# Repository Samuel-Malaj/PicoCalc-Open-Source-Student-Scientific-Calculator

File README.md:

# PicoCalc-Open-Source-Student-Scientific-Calculator
Open source scientific calculator built on Raspberry Pi Pico W — custom PCB, WiFi messaging, IR projector control and games.

# PicoCalc — Open Source Student Scientific Calculator

A fully custom scientific calculator built on the Raspberry Pi Pico W, designed specifically for students. Features wireless peer-to-peer messaging, IR classroom projector control, a custom PCB, and built-in games — all running on MicroPython.

---

## Overview

PicoCalc is an end-to-end hardware and software project encompassing PCB design, embedded systems programming, wireless networking, and circuit design. Every component — from the button matrix to the IR driver circuit — was designed, calculated, and implemented from scratch.

This project was built entirely by a Year 10/11 student as an independent engineering project.

---

## Features

### Scientific Calculator
- Full arithmetic operations with correct operator precedence
- Scientific functions: sin, cos, tan, log, ln, sqrt, powers, factorials
- Degree and radian mode switching
- Expression history and ANS recall
- Error handling for invalid inputs and edge cases
- Custom expression parser built from scratch in MicroPython

### Peer-to-Peer Messaging
- Send and receive text messages between two PicoCalc devices over WiFi
- UDP broadcast protocol for low-latency local communication
- Designed for classroom use — share working, answers, or notes with a friend

### IR Projector Control
- 940nm IR LED with BC547 transistor driver circuit
- Compatible with Hitachi, Maxell, Epson and Samsung projectors and displays
- Up to 10 metre range achieved through transistor amplification
- Allows students to control classroom projectors from their desk
- NEC and SIRC IR protocol support

### Games
- Built-in simple games for use during breaks
- Runs entirely on the calculator hardware — no additional software needed

---

## Hardware

### Custom PCB
- Designed from scratch in KiCad
- Manufactured by PCBWay
- 2-layer PCB with row traces on F.Cu and column traces on B.Cu
- Dimensions: 75.5mm × 146mm

### Components
| Component | Description |
|---|---|
| Raspberry Pi Pico W | Main microcontroller with WiFi and Bluetooth |
| 38× 6mm Tactile Switches | Button matrix (THT, through hole) |
| TSAL6200 | 940nm IR LED, 3mm horizontal |
| BC547 | NPN transistor for IR LED driver |
| 22Ω Resistor | IR LED current limiting |
| 1kΩ Resistor | Transistor base protection |
| 2.42" SSD1309 OLED | 128×64 I2C display |
| 2× AA Battery Holder | MPD BC2AAPC, powers via VSYS |

### Button Matrix
- 38 buttons arranged in a row/column matrix
- GP0–GP7: row outputs
- GP8–GP15: column inputs with internal pull-up resistors
- Only 16 GPIO pins required for 38 buttons
- Scanning rate fast enough to never miss a keypress

### IR LED Circuit
- VSYS (3V from 2× AA) powers the LED circuit
- 22Ω current limiting resistor → 82mA through LED
- BC547 transistor switches the high current safely
- GPIO only supplies <2.6mA to the base — well within Pico's 16mA limit

### Power
- 2× AA batteries connected to VSYS pin
- Auto power-off via MicroPython lightsleep after inactivity
- Lightsleep current draw: ~1-2mA — significantly extends battery life

---

## Software

### MicroPython
- Written entirely in MicroPython
- Modular codebase — calculator, display, networking, IR all separate modules
- Custom expression parser for evaluating scientific expressions
- Uses built-in `math` library for scientific functions

### WiFi Communication
- Both devices connect to the same network
- UDP sockets for low-latency message transmission
- Graceful handling of connection drops and reconnection

---

## PCB Design

Designed in KiCad. Key design decisions:

- **2-layer routing**: Row traces on F.Cu, column traces on B.Cu — allows the button matrix grid to work without short circuits
- **Through hole components**: All buttons and connectors are THT for mechanical strength under repeated use
- **RF keepout zone**: Respected around the Pico W antenna to preserve WiFi/BLE signal strength
- **Removable Pico**: THT header holes allow the Pico W to be plugged in and removed — not permanently soldered
- **Battery on reverse**: Battery holder mounted on B.Cu to keep the front face clean

---

## Schematic & Design Files

- KiCad schematic and PCB layout files included in `/hardware`
- Gerber files included in `/hardware/gerbers`
- BOM included in `/hardware/BOM.csv`

---

## What I Learned

- PCB design and manufacturing process (KiCad → Gerber → PCBWay)
- Ohm's law applied to real circuit design (resistor calculations for IR LED and transistor)
- Button matrix design — why a matrix uses N+M pins instead of N×M
- Two-layer PCB routing and via usage
- MicroPython embedded programming on real hardware
- WiFi networking with UDP sockets on microcontrollers
- IR remote control protocols (NEC, SIRC)
- Debugging real hardware and firmware issues

---

## Project Status

- [x] PCB designed and ordered
- [x] Schematic complete
- [ ] IR LED circuit designed and verified
- [x] MicroPython calculator engine
- [ ] Display driver integration
- [x] WiFi messaging
- [ ] IR control implementation
- [ ] Games

---

## License

MIT License — free to use, modify and build upon.

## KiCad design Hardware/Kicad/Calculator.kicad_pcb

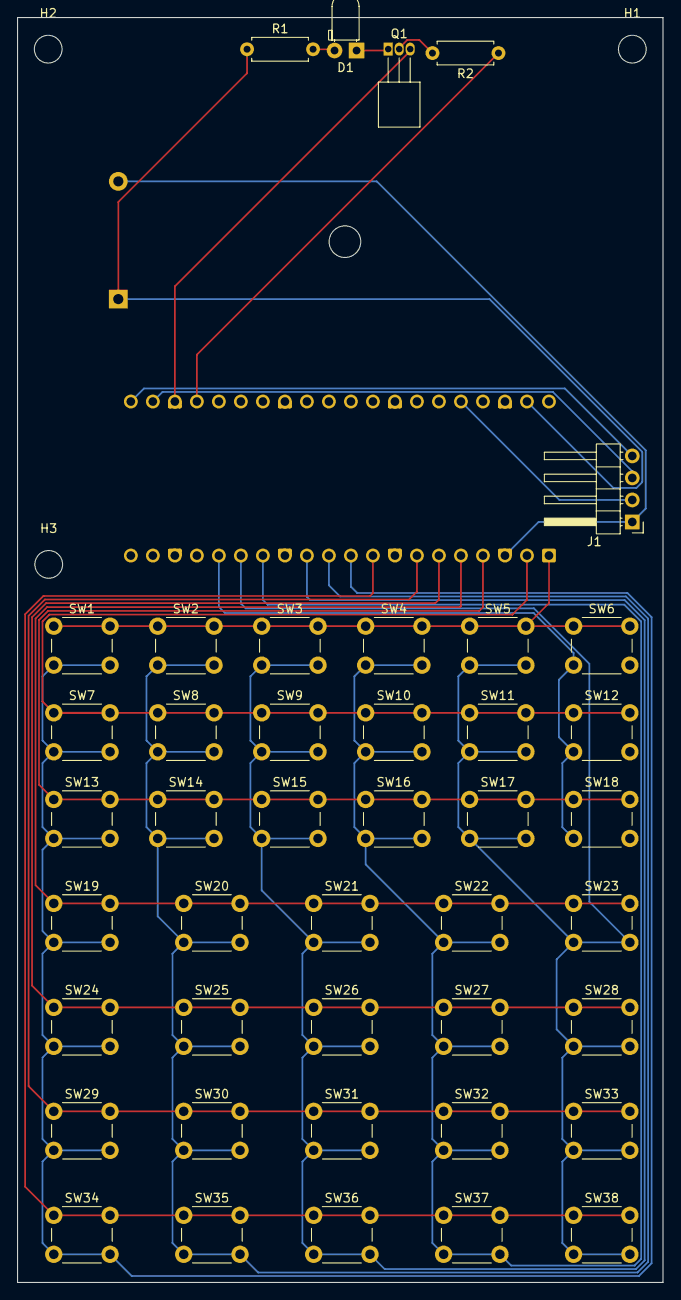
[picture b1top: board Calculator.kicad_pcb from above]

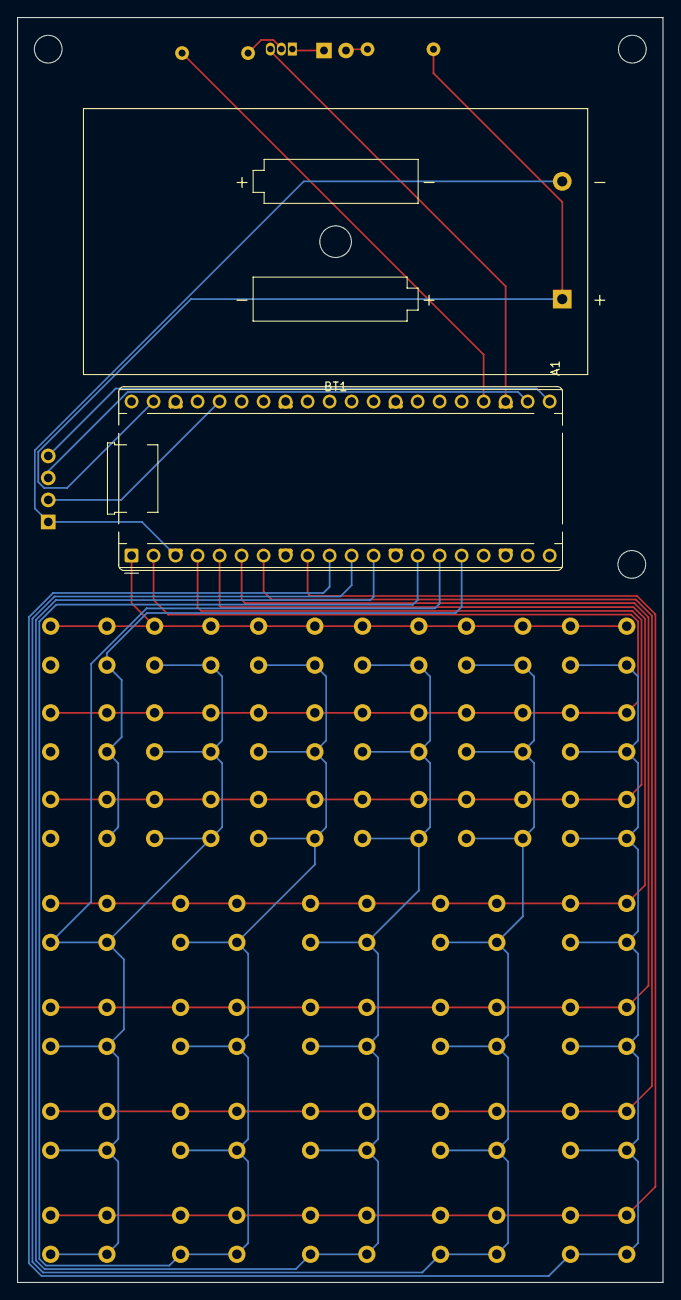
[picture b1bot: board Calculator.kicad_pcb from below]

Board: 2 copper layers, 74.5 x 146.0 mm, 48 parts (2 on the bottom side), 22 nets.

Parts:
A1: RaspberryPi_Pico_W; RaspberryPi_Pico_Common_THT
BT1: Battery; BatteryHolder_MPD_BC2AAPC_2xAA
D1: TSAL6200; LED_D3.0mm_Horizontal_O1.27mm_Z2.0mm_IRGrey
H1, H2, H3: MountingHole; MountingHole_3.2mm_M3
J1: Conn_01x04; PinHeader_1x04_P2.54mm_Horizontal
Q1: BC547; TO-92_Inline_Horizontal1
R1: 22R; R_Axial_DIN0207_L6.3mm_D2.5mm_P7.62mm_Horizontal
R2: 1000R; R_Axial_DIN0207_L6.3mm_D2.5mm_P7.62mm_Horizontal
SW1, SW2, SW3, SW4, SW5, SW6, SW7, SW8, SW9, SW10, SW11, SW12, SW13, SW14, SW15, SW16, SW17, SW18, SW19, SW20, SW21, SW22, SW23, SW24, SW25, SW26, SW27, SW28, SW29, SW30, SW31, SW32, SW33, SW34, SW35, SW36, SW37, SW38: SW_Push_Dual_x2; SW_PUSH_6mm_H4.3mm

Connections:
unnamed: A1.36 (3V3), J1.2
unnamed: A1.1 (GPIO0), SW1.1 (C), SW2.1 (C), SW3.1 (C), SW4.1 (C), SW5.1 (C), SW6.1 (C)
unnamed: A1.2 (GPIO1), SW7.1 (C), SW8.1 (C), SW9.1 (C), SW10.1 (C), SW11.1 (C), SW12.1 (C)
unnamed: A1.4 (GPIO2), SW13.1 (C), SW14.1 (C), SW15.1 (C), SW16.1 (C), SW17.1 (C), SW18.1 (C)
unnamed: A1.5 (GPIO3), SW19.1 (C), SW20.1 (C), SW21.1 (C), SW22.1 (C), SW23.1 (C)
unnamed: A1.6 (GPIO4), SW24.1 (C), SW25.1 (C), SW26.1 (C), SW27.1 (C), SW28.1 (C)
unnamed: A1.7 (GPIO5), SW29.1 (C), SW30.1 (C), SW31.1 (C), SW32.1 (C), SW33.1 (C)
unnamed: A1.9 (GPIO6), SW34.1 (C), SW35.1 (C), SW36.1 (C), SW37.1 (C), SW38.1 (C)
unnamed: A1.10 (GPIO7), SW1.2 (D), SW7.2 (D), SW13.2 (D), SW19.2 (D), SW24.2 (D), SW29.2 (D), SW34.2 (D)
unnamed: A1.11 (GPIO8), SW2.2 (D), SW8.2 (D), SW14.2 (D), SW20.2 (D), SW25.2 (D), SW30.2 (D), SW35.2 (D)
unnamed: A1.12 (GPIO9), SW3.2 (D), SW9.2 (D), SW15.2 (D), SW21.2 (D), SW26.2 (D), SW31.2 (D), SW36.2 (D)
unnamed: A1.14 (GPIO10), SW4.2 (D), SW10.2 (D), SW16.2 (D), SW22.2 (D), SW27.2 (D), SW32.2 (D), SW37.2 (D)
unnamed: A1.15 (GPIO11), SW5.2 (D), SW11.2 (D), SW17.2 (D), SW23.2 (D), SW28.2 (D), SW33.2 (D), SW38.2 (D)
unnamed: A1.16 (GPIO12), SW6.2 (D), SW12.2 (D), SW18.2 (D)
unnamed: A1.21 (GPIO16), J1.4
unnamed: A1.22 (GPIO17), J1.3
unnamed: A1.24 (GPIO18), R2.1
unnamed: A1.39 (VSYS), BT1.1 (+), R1.1
unnamed: A1.3 (GND), A1.8 (GND), A1.13 (GND), A1.18 (GND), A1.23 (GND), A1.28 (GND), A1.38 (GND), BT1.2 (-), J1.1, Q1.3 (E)
unnamed: D1.2 (A), R1.2
unnamed: D1.1 (K), Q1.1 (C)
unnamed: Q1.2 (B), R2.2

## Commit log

2026-03-22 Enhance README with detailed project information
    Expanded project overview, features, hardware, software, and lessons learned sections in README.
2026-03-22 Rename Calculator.kicad_pcb to Hardware/Kicad/Calculator.kicad_pcb
2026-03-22 Rename Calculator.kicad_pro to Hardware/Kicad/Calculator.kicad_pro
2026-03-22 Rename Calculator.kicad_sch to Hardware/Kicad/Calculator.kicad_sch
2026-03-22 Rename Hardware/Calculator-Gerber_Drills.zip to Hardware/gerbers/Calculator-Gerbers.zip
2026-03-22 Rename Hardware/Calculator-bottom-Top(pos).zip to Hardware/gerbers/Centroid.zip
2026-03-28 Add basic calculator functionality for addition and subtraction
    Implement a calculator that handles addition and subtraction of numbers represented as strings in a list. The program compresses adjacent numbers and performs operations iteratively until the express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
2026-03-28 Rename Calculate.py to Software/Calculate.py
2026-03-28 Add button press detection in main.py
    Implement button press detection using GPIO pins.
2026-03-28 Refactor calculation logic and add new functions
    Refactor calculation functions to improve readability and efficiency. Added compress_MultiplyDivide and get_compressed_MultiplyDivide functions for handling multiplication and division.
2026-03-29 Updated to incorporate calculations controlled by button presses
    Program now uses imputed button presses to calculate expression and output an answer
2026-03-29 Clean up Calculate.py by removing unused code
    Removed commented-out test code and adjusted return statement.
2026-03-29 Refactor scientific calculations and error handling
    Enhance scientific operator handling and improve error management.
2026-03-30 Enhanced calculator logic for indeces
2026-03-31 Enhance error handling in calculation methods and handles brackets
    Added error handling for various exceptions in calculation functions and improved the handling of mathematical errors.
2026-04-29 Refactor calculator input handling and button logic
2026-04-29 Refactor exponentiation handling in Calculate.py
    Removed decimal module usage for exponentiation and updated the handling of compressed values in the expression.
2026-05-04 Add Wi-Fi connection and character shift features
    Refactor main.py to include Wi-Fi functionality and shift character handling.
2026-05-08 Implement asyncio and socket for Wi-Fi text message communication
    Refactor calculator and character handling with asyncio for better concurrency and responsiveness and to allow simultaneous sending and receiving of text messages over Wi-Fi.
2026-05-10 new file for power management
    File allows Pico to switch of upon power button press
2026-05-10 Implement messaging and Power Off function
    Added use of socket and asyncio to simultaneously send and receive broadcasted UDP messages over Wi-Fi and implemented lowpower.py to allow pico to go into sleep mode upon press of power button.
2026-05-10 Update project status in README
2026-05-22 Updated to control OLED module and display inputs/outpus
    Incorporates OLED.py file defining simple functions to control OLED module, using SSD1309 driver, and display inputs and outputs
2026-05-23 new file to define icons
    file defines icons including Wi-Fi, No Wi-Fi and Shift icons to indicate to user if they are connected to the internet and if shift=True
2026-05-23 Refactor OLED display functions and add clear_main
    Added functions to clear the main display area and updated text display positions.
2026-05-23 Refactor main.py for enhanced functionality and display
    Updated calculator and character arrays to include new functions and improved display handling. Enhanced error handling and added WiFi connection features including WiFi icons and shift icon.
2026-05-26 Implement WhatsApp message sending feature
    Added functionality to send WhatsApp messages using an API.
2026-05-26 Added more python files for organisation
    Files pack most main.py functions into 3 separate files for tidier code. Functions including WiFi connectivity, mode functions, input functions and socket preparation.
2026-05-26 Refactor main function and clean up code
    Refactor main function and add new imports for inputs, WiFi, and modes. Remove unused variables and functions related to the calculator and messaging.
2026-05-26 clearing of OLED module between function change
2026-05-27 New icons added
    new icons such as 'No WiFi' icon and numerical indicator and alpha indicator to indicate to the user if the current input mode is numerical or alphabetical.
2026-05-27 Incorporated new Alpha, Numerical and No WiFi icon
2026-05-27 Refactor OLED display functions and add clear_mode_line
2026-05-27 Implement indicate_wifi function for OLED display
    Added indicate_wifi function to update Wi-Fi status on OLED display.
2026-05-27 Refactor main function for better clarity and flow
2026-05-27 Removed accidental changes to code
2026-05-28 fix: remove sensitive info
2026-05-28 Remove accidental change to modes.py and add new note_pad function.
    New note_pad function allows user to write and save a note to a text file.
2026-05-28 Refactor main.py and update Wi-Fi handling
    Refactor main.py to improve functionality and readability. Updated Wi-Fi connection checks and removed unused power_off function.
2026-05-28 Refactor Wi-Fi functions for better user experience
    Updated the Wi-Fi management functions to improve user interaction and feedback during network selection and connection processes.
2026-05-28 refactor: move power off function to utils.py
2026-05-28 refactor: remove unnecessary variables from modes.py
2026-05-28 fix: patch bug in messaging()
    Bug prevented Pico from receiving UDP messages. Pico can now simultaneously send and receive messages.
2026-05-28 Refactor WiFi module for improved functionality
2026-05-28 Refactor WiFi functions for improved clarity
2026-05-28 Remove prepare_socket() call from main function
    Removed the call to prepare_socket() in the main function.
2026-05-28 fix: patch bug in messaging()
    FIxed bug which prevented messaging() from being run multiple times as a result of the definition of variable stop_event. Bug now fixed.
2026-05-28 Feat: added new icons for different modes
2026-05-28 Feat: New main menu page
    Added main_main function to display icons for different modes and allow user to select from those modes
2026-05-28 Feat: implemented new main_menu function
    Main_menu function displays different icons for different modes and allows user to scroll through them and select a mode.
2026-05-29 feat: use framebuffer blit for faster icon rendering
2026-05-29 Refactor main_menu and update icon handling
    implements new function from icons.py to speed up processing and display of main menu icons to speed up scrolling.
2026-05-29 Feat: added new icons for different modes (whatsapp mode and games mode)
2026-05-29 feat: Add new options to main menu (whatsapp mode and games mode)
2026-05-30 Feat: Add new Tic Tac Toe grid, 'X', and 'O' icons
2026-05-30 Update inputs.py
    Added function select_num to limit user input for specific occasions
2026-05-30 Reorganize and restore functions in utils.py
2026-05-30 Add Games mode handling in main function
2026-05-30 Feat: add games functionality
    Created game_select function to allow user to select a game to play. Created Tic_Tac_Toe function as game option allowing the user to play tic tac toe/noughts and crosses
2026-05-30 Fix: patch bug in Tic Tac Toe + Feat: add tie recognition
2026-06-04 Refactor input handling and update arrays
2026-06-04 Refactor main_menu and button selection logic
    Refactor main_menu to use a list for modes and update button handling.
2026-06-04 Clean up main.py by removing comments and whitespace
    Removed commented setup instructions and unnecessary whitespace.
2026-06-04 Fix: patch bug in Tic Tac Toe
2026-06-04 Refactor main_menu and update modes list
2026-06-04 Add WiFi mode functionality to main.py
2026-06-06 Feat: add weather icons
2026-06-06 Feat: Add weather mode to main menu options
2026-06-06 Feat: add weather feature with location detection
    Added weather functionality including location detection and weather fetching.
2026-06-06 Feat: implement new weather funciton, wtth()
2026-06-06 Refactor modes.py for better memory management
    Refactor modes.py to improve memory management and structure.
2026-06-06 Rename wtth function to weather for clarity
